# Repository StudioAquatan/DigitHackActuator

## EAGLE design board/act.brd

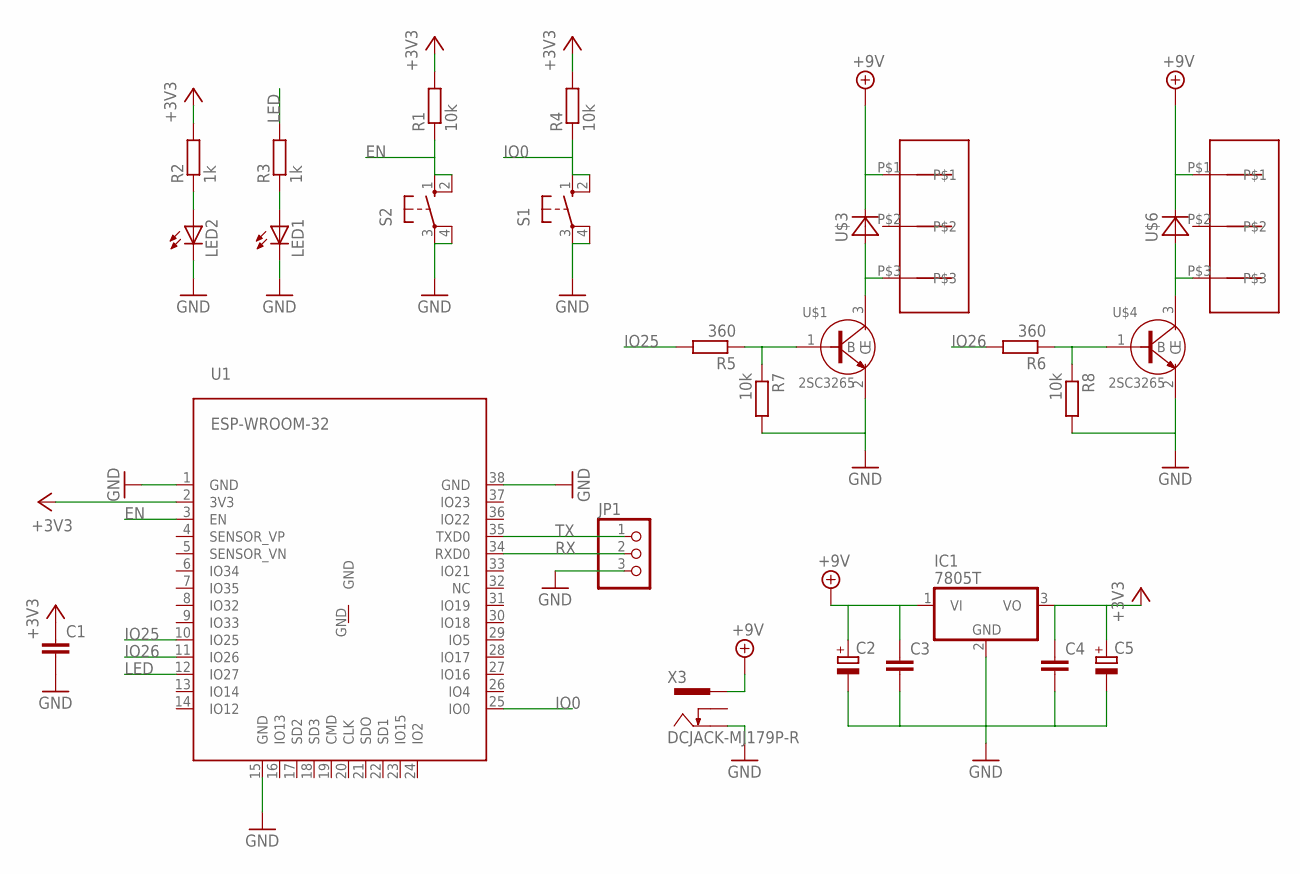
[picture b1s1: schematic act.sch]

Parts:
C1, C3, C4: C-EU050-024X044; C050-024X044
C2, C5: CPOL-EUE5-4; E5-4
IC1: 7805T; TO220H
JP1: PINHD-1X3/90; 1X03/90
LED1, LED2: LEDSML0603; SML0603
R1, R4, R7, R8: 10k; 0207/10
R2, R3: 1k; 0207/10
R5, R6: 360; 0207/10
S1, S2: 10-XX; B3F-10XX
U1: ESP-WROOM-32
U$1, U$4: 2SC3265; SC-59
U$2, U$5: JST_NH
U$3, U$6: GP20B
X3: DCJACK-MJ179P-R; MJ-179P-R

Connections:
+3V3: C1.1, C4.1, C5.+, IC1.3 (VO), R1.2, R2.2, R4.2, U1.2 (3V3)
+5V: LED2.A, R2.1
+5V1: LED1.A, R3.1
+9V: C2.+, C3.1, IC1.1 (VI), U$2.P$1, U$3.K (C), U$5.P$1, U$6.K (C), X3.1
EN: R1.1, S2.1 (S), S2.2 (S1), U1.3 (EN)
GND: C1.2, C2.-, C3.2, C4.2, C5.-, IC1.2 (GND), JP1.3, LED1.C, LED2.C, R7.2, R8.2, S1.3, S1.4 (P1), S2.3, S2.4 (P1), U1.1 (GND), U1.15 (GND), U1.38 (GND), U$1.2 (E), U$4.2 (E), X3.2; also elsewhere on the board
IO0: R4.1, S1.1 (S), S1.2 (S1), U1.25 (IO0)
IO16: U1.27 (IO16); also elsewhere on the board
IO25: R5.2, U1.10 (IO25)
IO26: R6.2, U1.11 (IO26)
LED: R3.2, U1.12 (IO27)
unnamed: U$1.3 (C), U$2.P$3, U$3.A
unnamed: U$4.3 (C), U$5.P$3, U$6.A
unnamed: R5.1, R7.1, U$1.1 (B)
unnamed: R6.1, R8.1, U$4.1 (B)
RX: JP1.2, U1.34 (RXD0)
TX: JP1.1, U1.35 (TXD0)

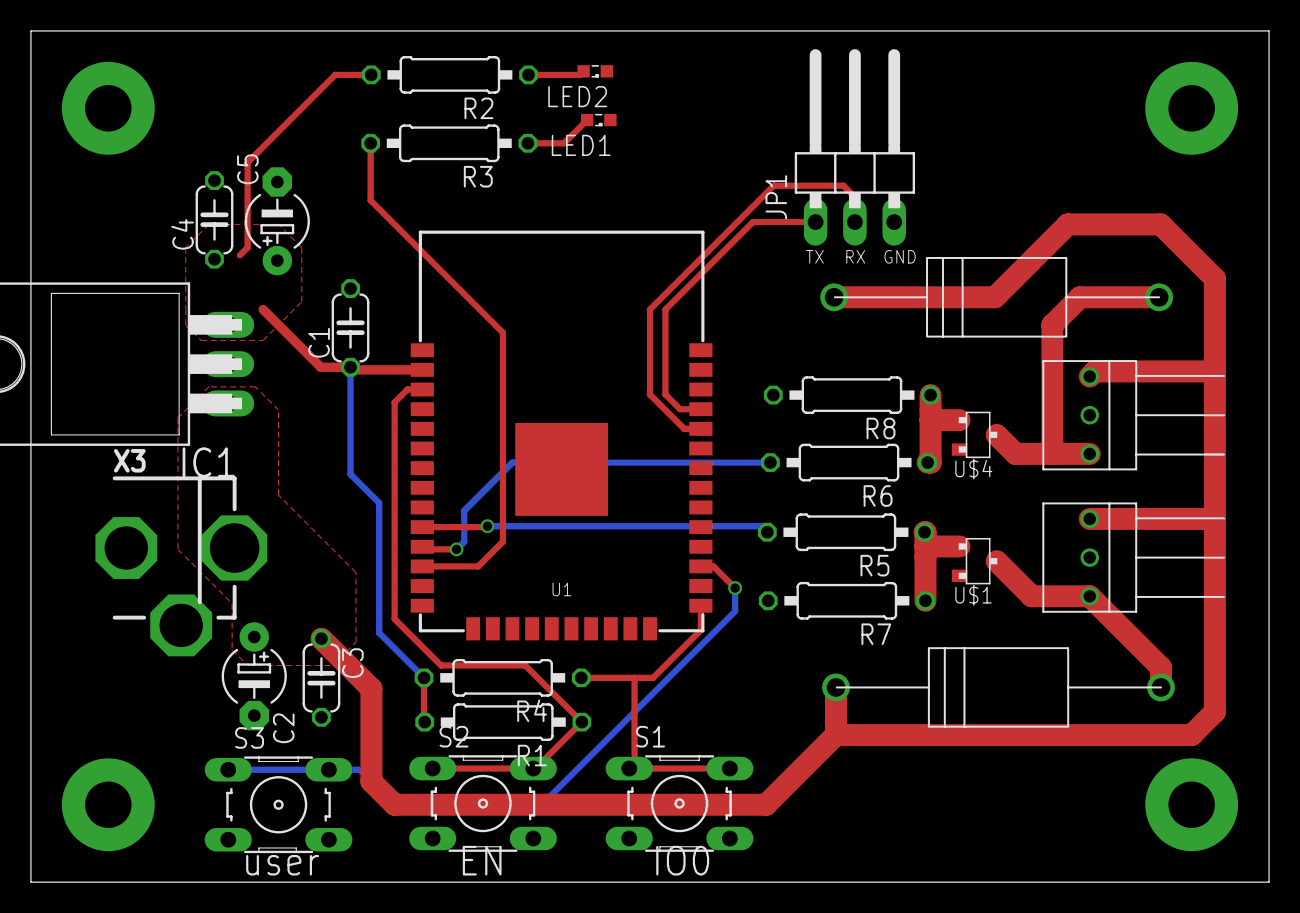
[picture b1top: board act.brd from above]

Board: 2 copper layers, 80.0 x 55.0 mm, 28 parts (0 on the bottom side), 17 nets.

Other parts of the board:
S3: B3F-10XX

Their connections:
GND: S3.3, S3.4; also elsewhere on the board
IO16: S3.1, S3.2; also elsewhere on the board

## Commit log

2018-05-24 add board
2018-05-25 add user_button
2018-06-07 add motor output program
2018-06-08 fix path
2018-06-08 reafactor
2018-06-08 ignore setting.h
2018-06-08 簡単なWebサーバを構築
2018-06-08 他のモジュールからの通信を元にモーターを動かす部分まで実装
